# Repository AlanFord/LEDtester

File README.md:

# An LED Test Tool
This project is a device allowing the user to set the brightness of an LED by setting the applied voltage
and reading the resulting resistor value needed for the desired brightness.

This project is derived from David Cook's excellent project documented at http://robotroom.com/LED-Tester-Pro-1.html.
While the board design for the David's project doesn't seem to be available, I've tried to recreate David's concept
(albeit with some of my own changes.)

David stated that he wasn't completely happy with the form factor of his LED Test Tool, so I went for a few changes:
* Many components are now surface mount, to save space and because I like to work with them;
* The microcontroller and the screen are no longer socketed, but rather soldered to the board;
* A programming header was added (needed since the microcontroller is no longer socketed);
* The programming header and the serial TX line were combined into a set of surface mount pads that can be connected with an SOIC test clip - see https://github.com/SimonMerrett/SOICbite
* A potentiometer was added to control the screen contrast;

All together these changes were problematic because more board edge space is now required for the
extra header and potentiometers.  Hence the board expanded somewhat.  It's still powered by a 9V
dry cell.  I thought of just using a 1.5V dry cell with a boost voltage converter, but that seemed to be
overkill for this project.

The board design is done in KiCad, because that's what I was taught over at Contextual Electronics.

## Board Dimensions
The original design appears to have used a pcb 2.1 in x 1.2 in (53.34 mm x 30.48 mm).  This included room 
for the two LED testing pads, each approximately 0.4 in by 0.5 in.  (I'm presuming all of the dimensions 
are in 0.1 in increments).  Room is also included for the LCD display, which in my case is 
40 mm wide by 30 mm deep (assuming the two eyelets on 
the bottom are bent down or removed).  The board is intended to be mounted on the side of a 9V battery, which
would have maximum dimensions of 48.50 mm tall by 26.5 mm wide.  The battery connection might be a two-terminal
screw connection (Digikey A98333-ND) with dimensions of 5.54 mm wide x 6.5 mm deep and pads with 1.1 mm
diameter holes.  Of course, it might also 
just be a soldered wire connection, but this pad size should accomodate both approaches.

The final board dimensions will have to accomodate the LED testing pads and the LCD display on the front
and the battery on the back.  Additional free space will likely be needed to accomodate the ISP header as
well as the potentiometer used for contrast control.

## ATTiny84 - Not a Lot of Pins
The ATTiny84 doesn't have a lot of pins to spare - after driving the LCD display with seven pins, one pin
for the TX line, and two pins for inputs from the LED, there is only one data line left over.  Not enough to
use a programming interface.  However, the advice found here https://www.avrfreaks.net/forum/can-i-reuse-isp-pins-other-taskstarget-atmega164p
indicates that the MISO, MOSI, and SCK programming lines can share pins with the LCD display
provided that 4.7K isolation resistors are used between the MCU and the LCD display.

## Configuring the ATTiny84
A number of references discuss the necessary support hardware to get an ATTiny84 going.  This includes
* A 0.1 uF cap between Vcc and GND, close to the chip (https://github.com/SpenceKonde/ATTinyCore)
* A larger power filtering cap on the Vcc line - the 1 uF cap in the design will do
* 4,5K resistors on loads connected to MOSI, MISO, and SCK (see above)
* 10K pull-up resistor on the RESET line

## Pins - the final definition
Three items need ADC connections - the LED low-side voltage monitor, the LED high-side voltage monitor, and the potentiometer used to set the desired LED voltage.  The ATTiny84 has ADC capability on all of the Port A pins, so that will 
tie up three of them.

The LCD data lines need (based on the library in use) four sequential pin numbers on a single bus.  Since I don't want to mess with the \~RESET line, that limits 
these pins to the Port A pins. 

That leaves us with us with four connections to go, the serial TX and three lines for the HD44780 LCD controller.  These connections are the Register Select (RS), the Read/Write (RW), and the Clock Enable (E).  
We have one on Port A and three on Port B (while avoiding the \~RESET line, PB3).  The last thing to factor
in is the fact that we will also be using the PA4, PA5, and PA6 pins for programming, so I don't want to 
be driving these pins with any voltage.  So here is the final layout -
* PA0     -> Voltage Control Input
* PA1     -> LED low Input
* PA2     -> LED high Input
* PA3     -> LCD Enable Output
* PA4-PA7 -> LCD Data Output
* PB0     -> LCD RS Output
* PB1     -> LCD RW Output
* PB2     -> Serial Output

## HD44780 LCD Controller Connections
The pinout for the HD44780 can be found at https://en.wikipedia.org/wiki/Hitachi_HD44780_LCD_controller
but I'll repeat it here.
* Pin Layout
*  1  2
*  3  4
*  5  6
*  7  8
*  9  10
*  11 12
*  13 14
* Pin Definitions
* 1  -> Ground
* 2  -> VCC (+3.3V to +5V)
* 3  -> Contrast Adjustment
* 4  -> Register Select (RS)
* 5  -> Read/Write (RW)
* 6  -> Clock Enable (E)
* 7  -> Not Used
* 8  -> Not Used
* 9  -> Not Used
* 10 -> Not Used
* 11 -> Bit 4
* 12 -> Bit 5
* 13 -> Bit 6
* 14 -> Bit 7
* 15 -> Backlight Anode (+) [not available on my board]
* 16 -> Backlight Cathode (-) [not available on my board]

##  Are You Serial !?!?
The ATTiny84 doesn't have real USART capability, but does have a Universal Serial Interface.  This feature
is more efficient that bit-banging a software serial line, but the output is restricted to a specific pin,
making it hard to fit everything else in.  Thus, this design does not use the USI and does serial the 
hard way.  This limits us to a slow speed of 9600 baud.  But since this feature is primarily for debugging,
it's no great loss.

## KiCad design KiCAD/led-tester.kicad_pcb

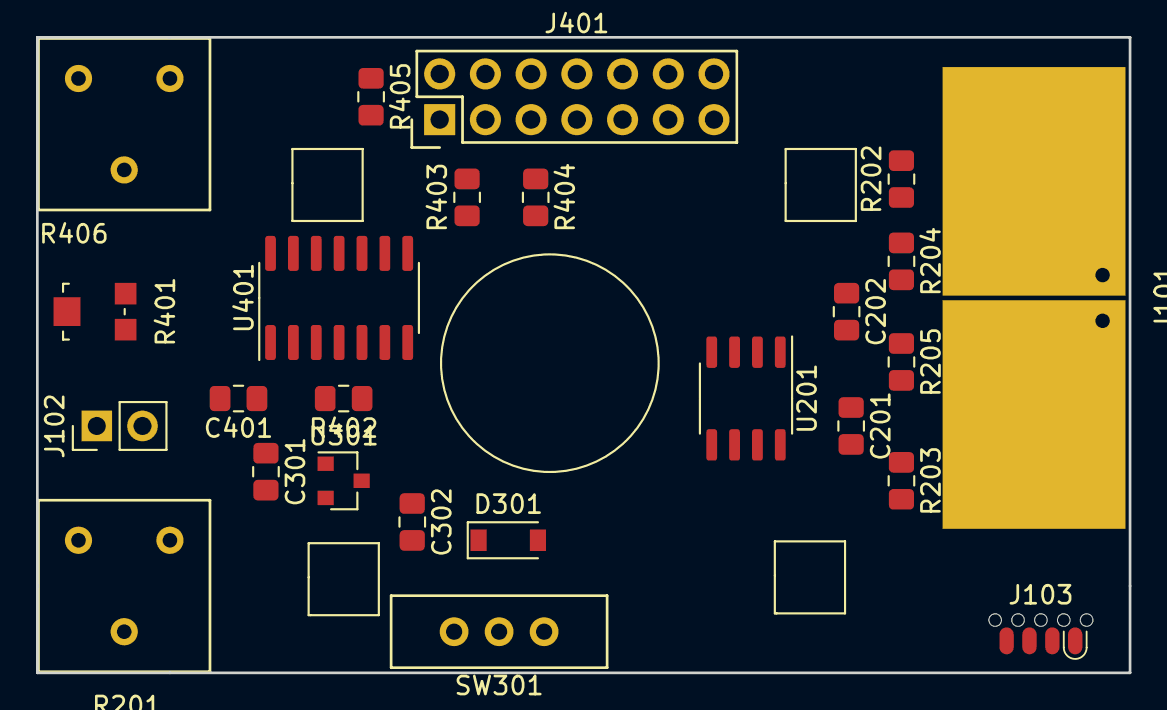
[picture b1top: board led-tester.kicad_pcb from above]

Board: 2 copper layers, 60.7 x 35.3 mm, 25 parts (0 on the bottom side), 24 nets, no tracks yet.

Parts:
C201, C202, C302: 0.1uF; C_0805_2012Metric_Pad1.15x1.40mm_HandSolder
C301: 2.2 uF; C_0805_2012Metric_Pad1.15x1.40mm_HandSolder
C401: 0.1 uF; C_0805_2012Metric_Pad1.15x1.40mm_HandSolder
D301: Schottky; D_SOD-123
J101: NOPOP; LED-LargePads
J102: NOPOP; PinHeader_1x02_P2.54mm_Vertical
J103: Conn_02x04_Counter_Clockwise; SOIC_clipProgSmall
J401: Conn_02x07_Odd_Even; Pololu_diplay_2x07
R201: 500R; bourns_3386_potentiometer
R202, R203: 47R; R_0805_2012Metric_Pad1.15x1.40mm_HandSolder
R204, R205, R402: 10K; R_0805_2012Metric_Pad1.15x1.40mm_HandSolder
R401: 10k; Panasonic_pot
R403, R404, R405: 4.5K; R_0805_2012Metric_Pad1.15x1.40mm_HandSolder
R406: 10k; bourns_3386_potentiometer
SW301: SWITCH_SPDT; SPDT-switch
U201: LM317L; SO-8_3.9x4.9mm_P1.27mm
U301: MCP1702; SOT-23
U401: ATtiny84A-SSU; SOIC-14_3.9x8.7mm_P1.27mm

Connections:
+5V: C301.1, C401.1, J103.1, J401.2, R401.3, R402.2, R406.3, U301.2, U401.1
+9V: C302.1, D301.1, U201.1, U301.3
/Digital Display/CE: J401.6, U401.10
/Digital Display/LEDhigh: C202.1, R204.2, R205.1, U401.11
/Digital Display/MISO: J103.6, R404.2, U401.8
/Digital Display/MOSI: J103.5, R403.1, U401.7
/Digital Display/RESET: J103.8, R402.1, U401.4
/Digital Display/RS: J401.4, U401.2
/Digital Display/RW: J401.5, U401.3
/Digital Display/SCK: J103.7, R405.2, U401.9
/Digital Display/TX: J103.3, U401.5
/Digital Display/a11: J401.11, R405.1
/Digital Display/a12: J401.12, R404.1
/Digital Display/a13: J401.13, R403.2
/Digital Display/a14: J401.14, U401.6
/current_sensor/LED+: J101.1, R202.1, R204.1, U201.4
/current_sensor/LED-: C201.1, J101.2, R203.1, R205.2, U401.12
/power/Battery+: J102.1, SW301.1
GND: C201.2, C202.2, C301.2, C302.2, C401.2, J102.2, J103.4, J401.1, R203.2, R401.1, R406.1, U301.1, U401.14
unnamed: D301.2, SW301.2
unnamed: J401.3, R401.2
unnamed: R201.2, U201.2, U201.3, U201.6, U201.7
unnamed: R201.3, R202.2
unnamed: R406.2, U401.13

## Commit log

2016-05-25 First real commit of the LEDtester software and board design
2016-06-04 update to use ATTiny1634 mcu
2016-06-16 added footprint for led test pads and added pin numbers
2016-06-16 changed board setting to be compatible with OSHPark
2016-06-23 added footprints
2016-06-23 cleaned up local footprint library
2016-06-23 updated project to include new footprints
2016-07-10 converted to hierarchical sheets and added MPN field to components
2016-07-10 moved mcu and display to separate sheet
2016-07-12 reorganized digitalDisplay sheet and pulled LED pads to top sheet
2016-07-12 corrected pin connections on ATTiny1634
2016-07-12 improved pads for LCD display and LED test pads
2016-07-12 updated netlist and started pcb layout
2016-08-06 updated files
2016-08-06 tried to fix the GND "not driven" messages. Only moderately successful.
2019-06-11 rebooting the project
2019-07-14 switching back to an ATTiny84 or ATTiny84A
2019-07-14 changing pins to accomodate the ATTiny84
2019-07-19 clean up pin defines
2019-07-20 Regenerated the netlist
